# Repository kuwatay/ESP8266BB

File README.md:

# ESP8266-BB

## 1. Introduction

**ESP8266-BB** (Bearbone) is yet another ESP-8266 based development board. 
For the programming of the board, an *extended 7-pin FTDI adapter* is required.

## 2. Schematic

## 3. Board layout

## 4. BOM

|     Name   |          Parts                    |   Value                 |
|  :-------: | :-------------------------------: | :---------------------: |
|     U1     |  3.3V Low voltage drop Regulator  | LM1117-3.3              | 
|     U2     |  ESP-WROOM-02                     | -                       | 
|  LED1,LED2 |  LED1 (Green)  LED2(RED)          | (1608 size)             | 
|     J1     |  2.1mm power Jack                 | Power in                | 
|     J2     |  7 pin                            | L-angle connector       | 
|   J3,J4    |  10Pin receptacle                 | pin header is ok        | 
|  SW1,SW2   |  Tactile Switch                   | Alps SKHH or equivalent | 
|   Q1,Q2    |  NPN-TR                           | (2SC2712)               | 
|   R1-R5    |  Carbon Register                  | 10K Ohm 1/10W(1608)     | 
|   R6,R7    |  Carbon Register                  | 1K Ohm 1/10W(1608)      | 
|   R9,R11   |  Carbon Register                  | 10K Ohm 1/10W(1608)     | 
|   R8,R12   |  Carbon Register                  | 1K Ohm 1/10W(1608)      | 
|     C1     |  Electrolytic  Capacitor          | 10uF / 10V or better    |
|     C2     |  Electrolytic  Capacitor          | 100uF / 10V or better   |
|     C3     |  Multilayer Ceramic  Capacitor    | 0.01uF / 10V (1608)     |
|     C4     |  Multilayer Ceramic  Capacitor    | 0.1uF / 10V (1608)      |

## EOF

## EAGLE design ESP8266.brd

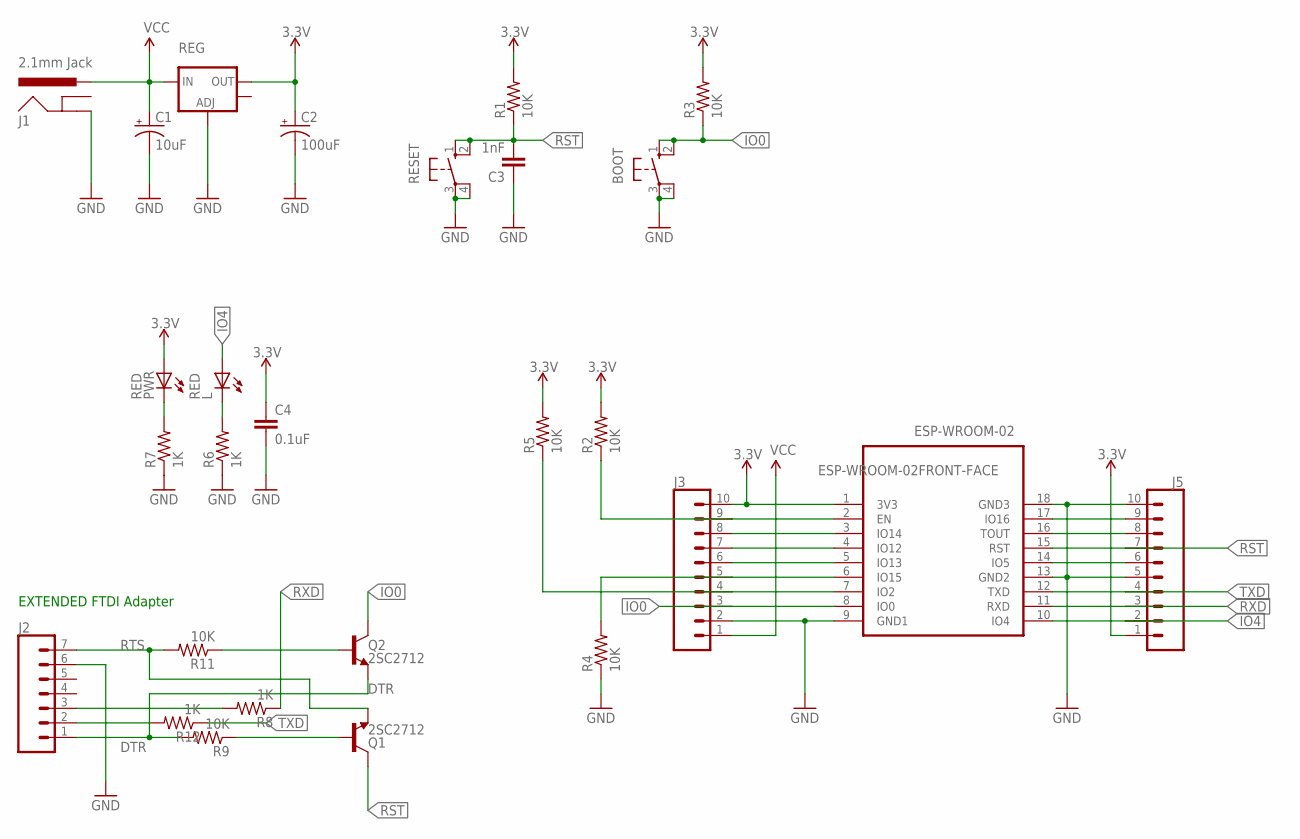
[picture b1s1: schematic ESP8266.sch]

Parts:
BOOT: 10-XX; B3F-10XX
C1: 10uF; PANASONIC_D
C2: 100uF; PANASONIC_D
C3: 1nF; 0805
C4: 0.1uF; 0805
ESP-WROOM-02: ESP-WROOM-02FRONT-FACE; FRONT-FACE
J1: 2.1mm Jack; POWER_JACK_PTH_LOCK
J2: CONN_07LOCK; 1X07_LOCK
J3, J5: CONN_10"; 1X10
L: RED; CHIP-LED0805
PWR: RED; CHIP-LED0805
Q1, Q2: 2SC2712; SOT23-3
R1, R2, R3, R4, R5, R9, R11: 10K; 0805
R6, R7, R8, R12: 1K; 0805
REG: V_REG_LM1117SOT223; SOT223
RESET: 10-XX; B3F-10XX

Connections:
3.3V: C2.+, C4.1, ESP-WROOM-02.1 (3V3), J3.10, J5.1, PWR.A, R1.2, R2.2, R3.2, R5.2, REG.2 (OUT)
B: Q2.1 (B), R11.1
DTR: J2.1, Q2.2 (E), R9.2
EN: ESP-WROOM-02.2 (EN), J3.9, R2.1
GND: BOOT.3, BOOT.4 (P1), C1.-, C2.-, C3.1, C4.2, ESP-WROOM-02.9 (GND1), ESP-WROOM-02.13 (GND2), ESP-WROOM-02.18 (GND3), J1.GND, J2.6, J3.2, J5.5, J5.10, R4.1, R6.1, R7.1, REG.1 (ADJ), RESET.3, RESET.4 (P1)
IO0: BOOT.1 (S), BOOT.2 (S1), ESP-WROOM-02.8 (IO0), J3.3, Q2.3 (C), R3.1
IO4: ESP-WROOM-02.10 (IO4), J5.2, L.A
unnamed: J2.2, R12.2
unnamed: J2.3, R8.2
unnamed: Q1.1 (B), R9.1
unnamed: ESP-WROOM-02.3 (IO14), J3.8
unnamed: ESP-WROOM-02.4 (IO12), J3.7
unnamed: ESP-WROOM-02.5 (IO13), J3.6
unnamed: ESP-WROOM-02.6 (IO15), J3.5, R4.2
unnamed: ESP-WROOM-02.7 (IO2), J3.4, R5.1
unnamed: PWR.C, R7.2
unnamed: L.C, R6.2
unnamed: ESP-WROOM-02.17 (IO16), J5.9
unnamed: ESP-WROOM-02.16 (TOUT), J5.8
unnamed: ESP-WROOM-02.14 (IO5), J5.6
RST: C3.2, ESP-WROOM-02.15 (RST), J5.7, Q1.3 (C), R1.1, RESET.1 (S), RESET.2 (S1)
RTS: J2.7, Q1.2 (E), R11.2
RXD: ESP-WROOM-02.11 (RXD), J5.3, R8.1
TXD: ESP-WROOM-02.12 (TXD), J5.4, R12.1
VCC: C1.+, J1.PWR, J3.1, REG.3 (IN)

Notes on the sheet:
EXTENDED FTDI Adapter

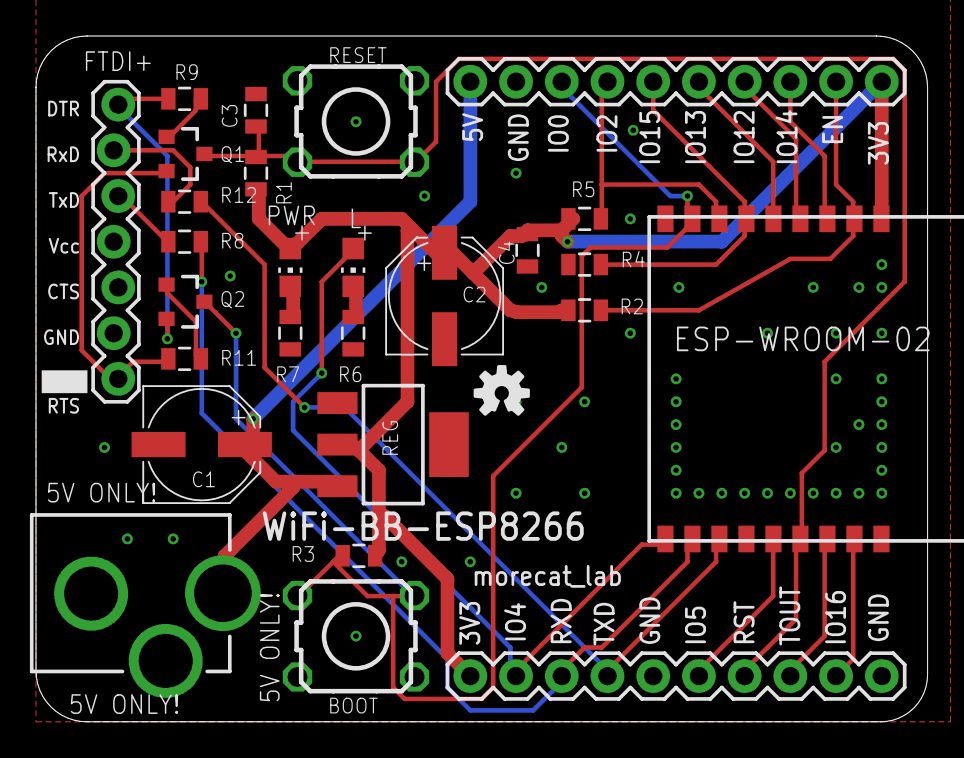
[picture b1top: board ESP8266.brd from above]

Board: 4 copper layers, 49.5 x 38.1 mm, 29 parts (1 on the bottom side), 25 nets.

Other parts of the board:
U$2, U$3: OSHW-LOGO-S

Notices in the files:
parts and their libraries:
SparkFun-Connectors: Licensing: CC v3.0 Share-Alike You are welcome to use this library for commercial purposes.
SparkFun-DiscreteSemi: Licensing: Creative Commons ShareAlike 4.0 International - https://creativecommons.org/licenses/by-sa/4.0
